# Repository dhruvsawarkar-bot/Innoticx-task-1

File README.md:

# Innoticx-task-1
Smart Home automation system using ESP32.

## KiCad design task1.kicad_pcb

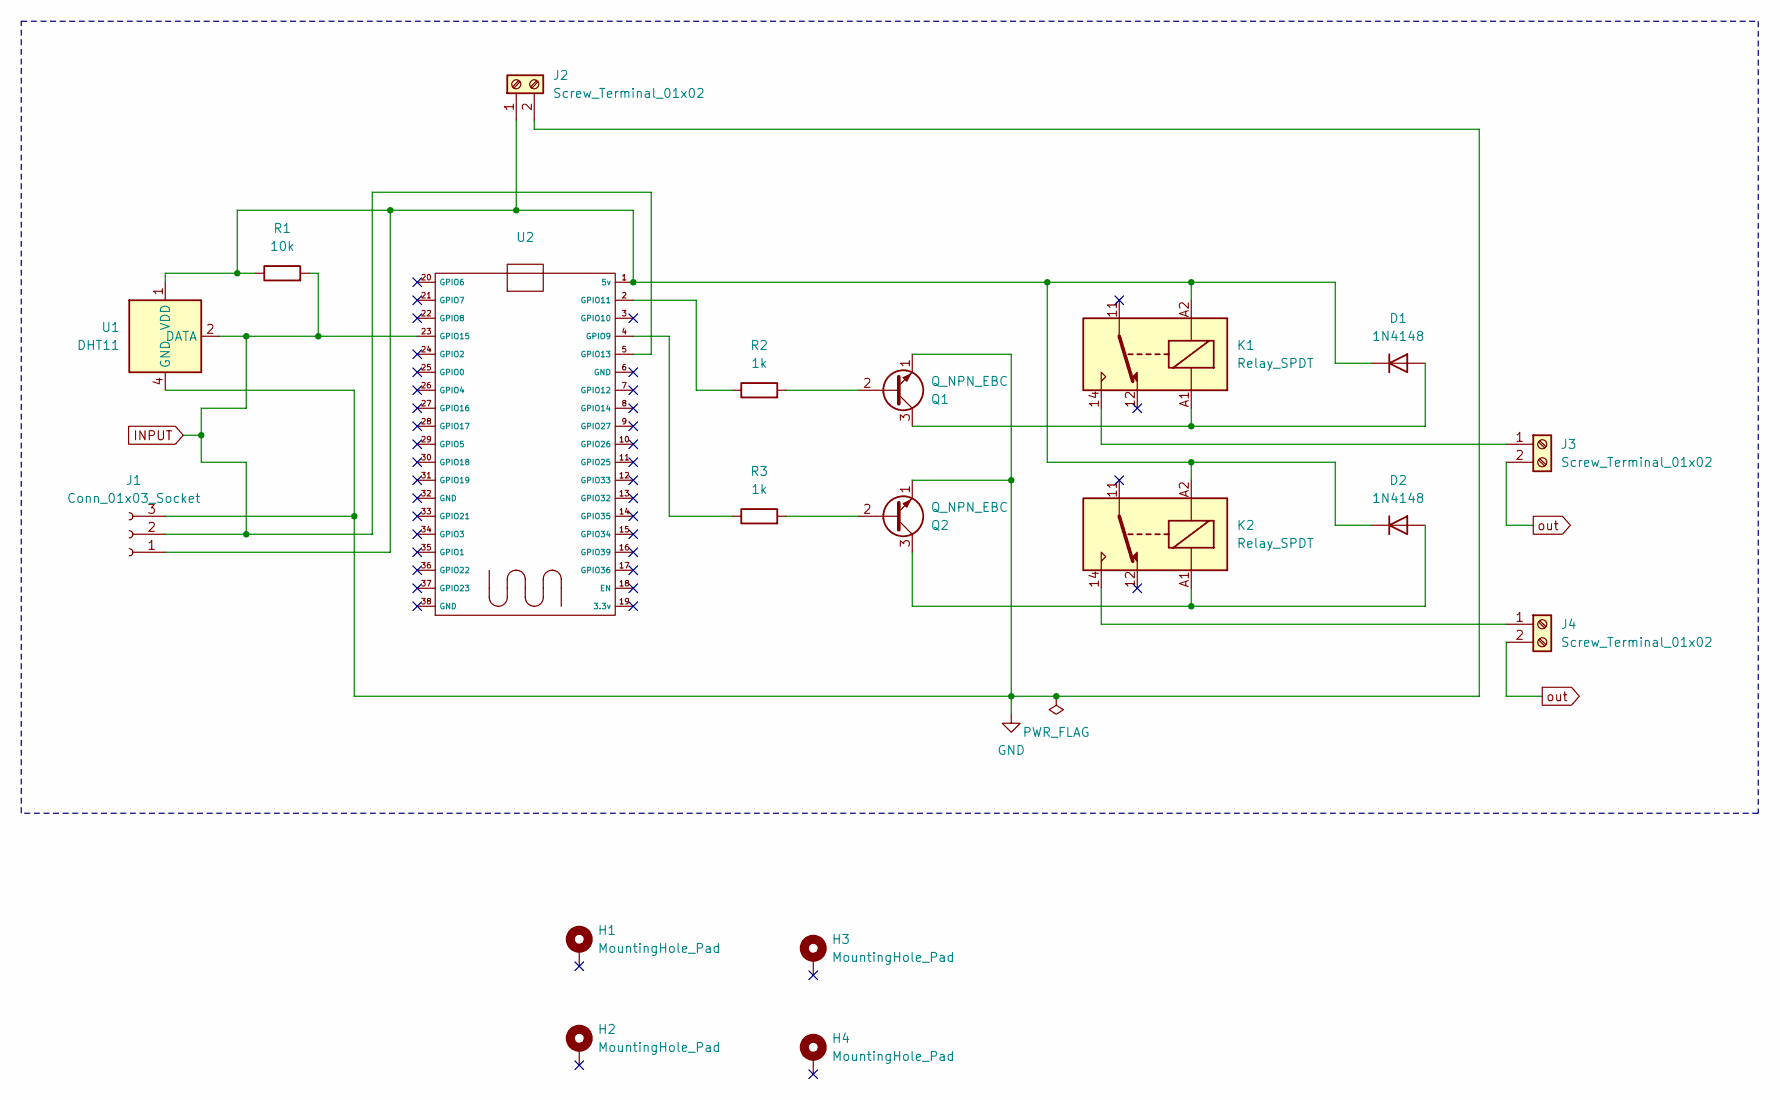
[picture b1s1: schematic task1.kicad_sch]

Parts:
D1, D2: 1N4148; D_DO-35_SOD27_P7.62mm_Horizontal
H1, H2, H3, H4: MountingHole_Pad; MountingHole_2.2mm_M2_Pad_Via
J1: Conn_01x03_Socket; PinHeader_1x03_P2.54mm_Vertical
J2, J3, J4: Screw_Terminal_01x02; TerminalBlock_bornier-2_P5.08mm
K1, K2: Relay_SPDT; Relay_SPDT_Finder_40.31
Q1, Q2: Q_NPN_EBC; TO-92_HandSolder
R1: 10k; R_Axial_DIN0207_L6.3mm_D2.5mm_P10.16mm_Horizontal
R2, R3: 1k; R_Axial_DIN0207_L6.3mm_D2.5mm_P10.16mm_Horizontal
U1: DHT11; Aosong_DHT11_5.5x12.0_P2.54mm
U2: ESP32_38pin

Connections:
GND: J1.3, J2.2, Q1.1 (E), Q2.1 (E), U1.4 (GND)
INPUT: J1.2, R1.2, U1.2 (DATA), U2.5 (GPIO13), U2.23 (GPIO15)
unnamed: D1.2 (A), K1.A1, Q1.3 (C)
unnamed: D1.1 (K), D2.1 (K), J1.1, J2.1, K1.A2, K2.A2, R1.1, U1.1 (VDD), U2.1 (5v)
unnamed: D2.2 (A), K2.A1, Q2.3 (C)
unnamed: J3.1, K1.14
unnamed: J4.1, K2.14
unnamed: Q1.2 (B), R2.2
unnamed: Q2.2 (B), R3.2
unnamed: R3.1, U2.4 (GPIO9)
unnamed: R2.1, U2.2 (GPIO11)
out: J3.2, J4.2

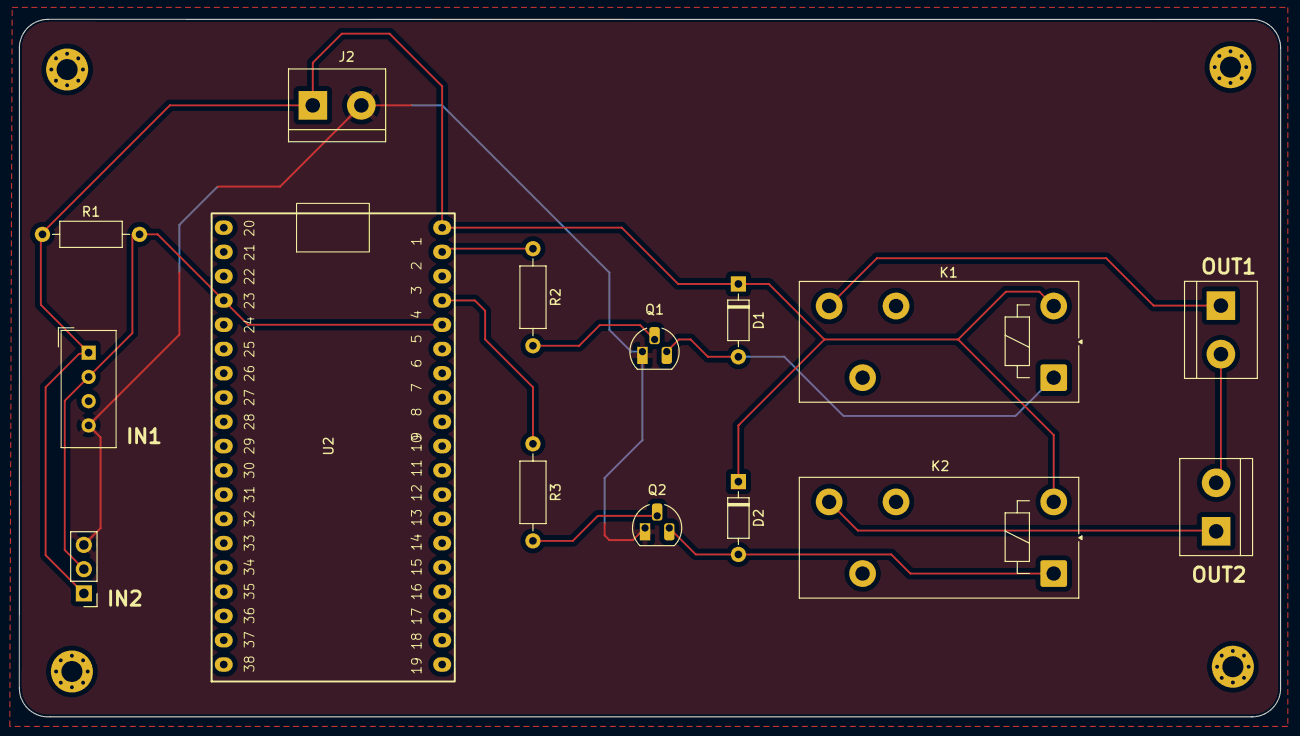
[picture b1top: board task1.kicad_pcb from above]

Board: 2 copper layers, 132.0 x 73.0 mm, 19 parts (0 on the bottom side), 12 nets.
